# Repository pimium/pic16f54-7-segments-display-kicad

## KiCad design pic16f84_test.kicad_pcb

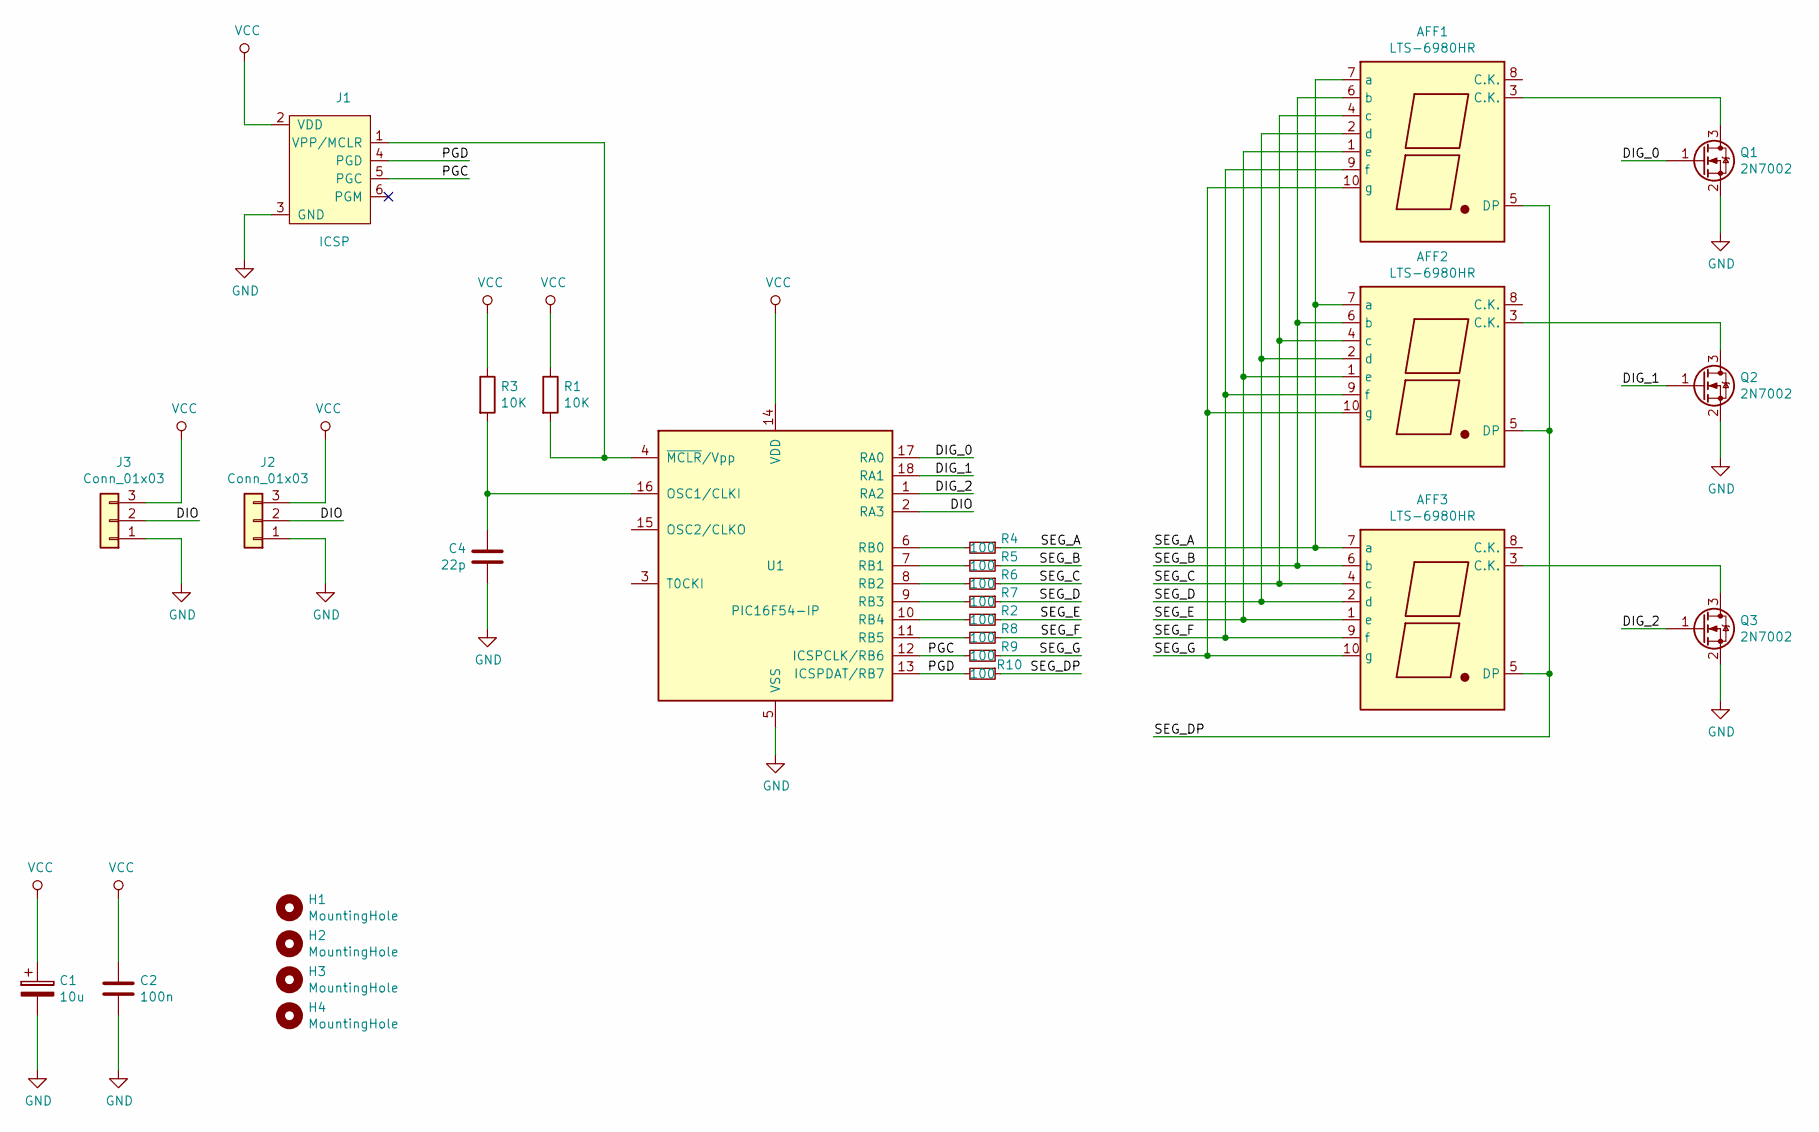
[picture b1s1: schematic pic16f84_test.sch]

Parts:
AFF1, AFF2, AFF3: LTS-6980HR; 7SegmentLED_LTS6760_LTS6780
C1: 10u; CP_EIA-3216-18_Kemet-A_Pad1.58x1.35mm_HandSolder
C2: 100n; C_0805_2012Metric_Pad1.15x1.40mm_HandSolder
C4: 22p; C_0805_2012Metric_Pad1.15x1.40mm_HandSolder
H1, H2, H3, H4: MountingHole; MountingHole_3.2mm_M2
J1: ICSP; PinHeader_1x06_P2.54mm_Vertical
J2, J3: Conn_01x03; PinHeader_1x03_P2.54mm_Vertical
Q1, Q2, Q3: 2N7002; SOT-23
R1, R3: 10K; R_0603_1608Metric_Pad1.05x0.95mm_HandSolder
R2, R4, R5, R6, R7, R8, R9, R10: 100; R_0603_1608Metric_Pad1.05x0.95mm_HandSolder
U1: PIC16F54-IP; SOP-18_7.0x12.5mm_P1.27mm

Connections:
/DIG_0: Q1.1 (G), U1.17 (RA0)
/DIG_1: Q2.1 (G), U1.18 (RA1)
/DIG_2: Q3.1 (G), U1.1 (RA2)
/DIO: J2.2, J3.2, U1.2 (RA3)
/PGC: J1.5 (PGC), R9.2, U1.12 (ICSPCLK/RB6)
/PGD: J1.4 (PGD), R10.2, U1.13 (ICSPDAT/RB7)
/SEG_A: AFF1.7 (a), AFF2.7 (a), AFF3.7 (a), R4.1
/SEG_B: AFF1.6 (b), AFF2.6 (b), AFF3.6 (b), R5.1
/SEG_C: AFF1.4 (c), AFF2.4 (c), AFF3.4 (c), R6.1
/SEG_D: AFF1.2 (d), AFF2.2 (d), AFF3.2 (d), R7.1
/SEG_DP: AFF1.5 (DP), AFF2.5 (DP), AFF3.5 (DP), R10.1
/SEG_E: AFF1.1 (e), AFF2.1 (e), AFF3.1 (e), R2.1
/SEG_F: AFF1.9 (f), AFF2.9 (f), AFF3.9 (f), R8.1
/SEG_G: AFF1.10 (g), AFF2.10 (g), AFF3.10 (g), R9.1
GND: C1.2, C2.2, C4.2, J1.3 (GND), J2.1, J3.1, Q1.2 (S), Q2.2 (S), Q3.2 (S), U1.5 (VSS)
unnamed: AFF1.3 (C.K.), Q1.3 (D)
unnamed: AFF2.3 (C.K.), Q2.3 (D)
unnamed: AFF3.3 (C.K.), Q3.3 (D)
unnamed: C4.1, R3.2, U1.16 (OSC1/CLKI)
unnamed: J1.1 (VPP/MCLR), R1.2, U1.4 (~MCLR~/Vpp)
unnamed: R2.2, U1.10 (RB4)
unnamed: R4.2, U1.6 (RB0)
unnamed: R5.2, U1.7 (RB1)
unnamed: R6.2, U1.8 (RB2)
unnamed: R7.2, U1.9 (RB3)
unnamed: R8.2, U1.11 (RB5)
VCC: C1.1, C2.1, J1.2 (VDD), J2.3, J3.3, R1.1, R3.1, U1.14 (VDD)

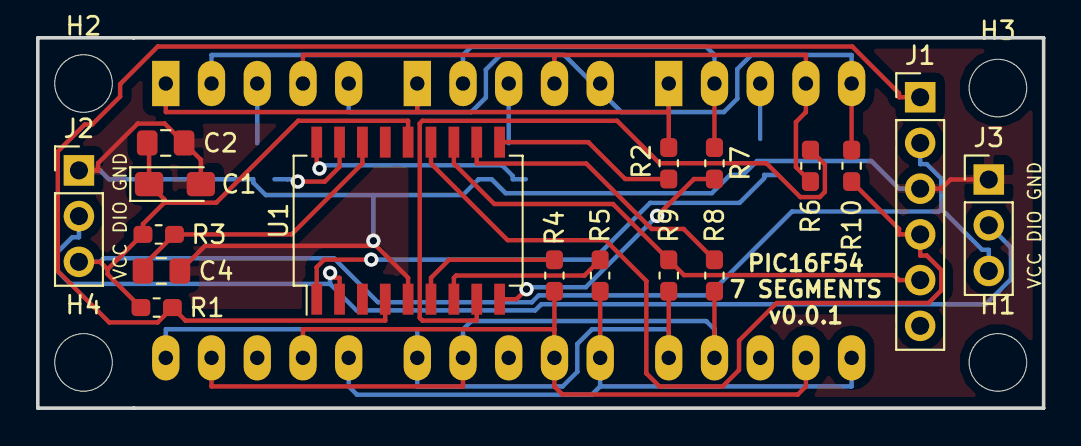
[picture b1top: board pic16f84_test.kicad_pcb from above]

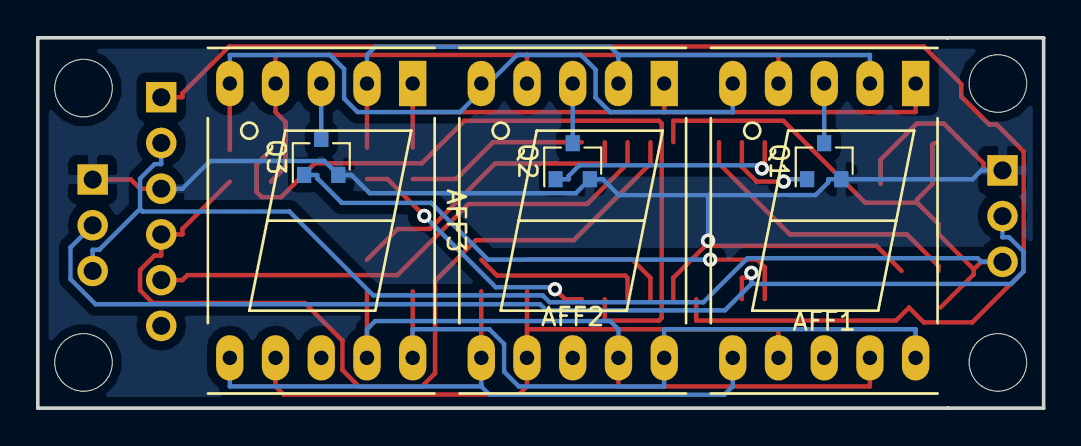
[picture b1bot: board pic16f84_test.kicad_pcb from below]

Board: 2 copper layers, 55.9 x 20.6 mm, 27 parts (6 on the bottom side), 27 nets.

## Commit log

2020-06-28 my first commit
2020-06-28 my first commit
    Changes to be committed:
    new file: .gitattributes
    new file: .gitignore
    new file: pic16f84_test-cache.lib
    new file: pic16f84_test.kicad_pcb
    new file: pic16f84_test.pro
2020-06-28 done with revision 0.01
2020-06-28 augment the diameter of the mounting holes
2020-07-16 just 3 segments
2021-12-06 add pictures
